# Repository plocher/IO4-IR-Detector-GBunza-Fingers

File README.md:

# IO4-IR-Detector-GBunza-Fingers
## License: CERN Open Hardware Licence v1.2

IR Detector subassemblies made to look like N or HO scale ties.

Works with GBunza\'s MRCS [MRCS-DAPD](/pages/MRCS-DAPD) and SPCoast [IO4-IR-Detector-GBunza](/pages/IO4-IR-Detector-GBunza) passive IR Detectors

  * E1C is the Ambient transistor, labeled T1 on the MRCS schematic.
  * E2C is the between the rails detector transistor.
  * Fab with a BLACK silk screen to help blend in to the trackwork.
  * Cut to length for N scale

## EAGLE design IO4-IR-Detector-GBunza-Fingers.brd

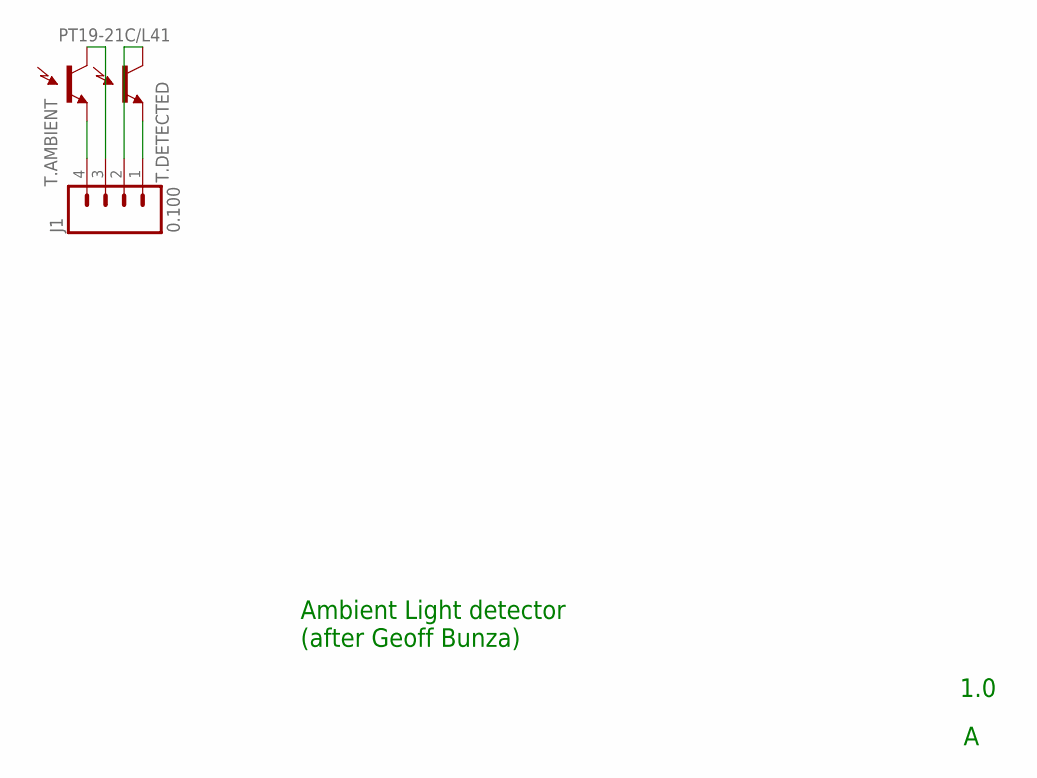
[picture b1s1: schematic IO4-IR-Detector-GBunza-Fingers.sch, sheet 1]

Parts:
J1: 0.100; 1X04_LOCK
T.AMBIENT, T.DETECTED: PT19-21C/L41; ALS-PT19

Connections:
unnamed: J1.4, T.AMBIENT.E (E1)
unnamed: J1.1, T.DETECTED.E (E1)
unnamed: J1.2, T.DETECTED.C (C1)
unnamed: J1.3, T.AMBIENT.C (C1)

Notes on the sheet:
Ambient Light detector (after Geoff Bunza)
1.0

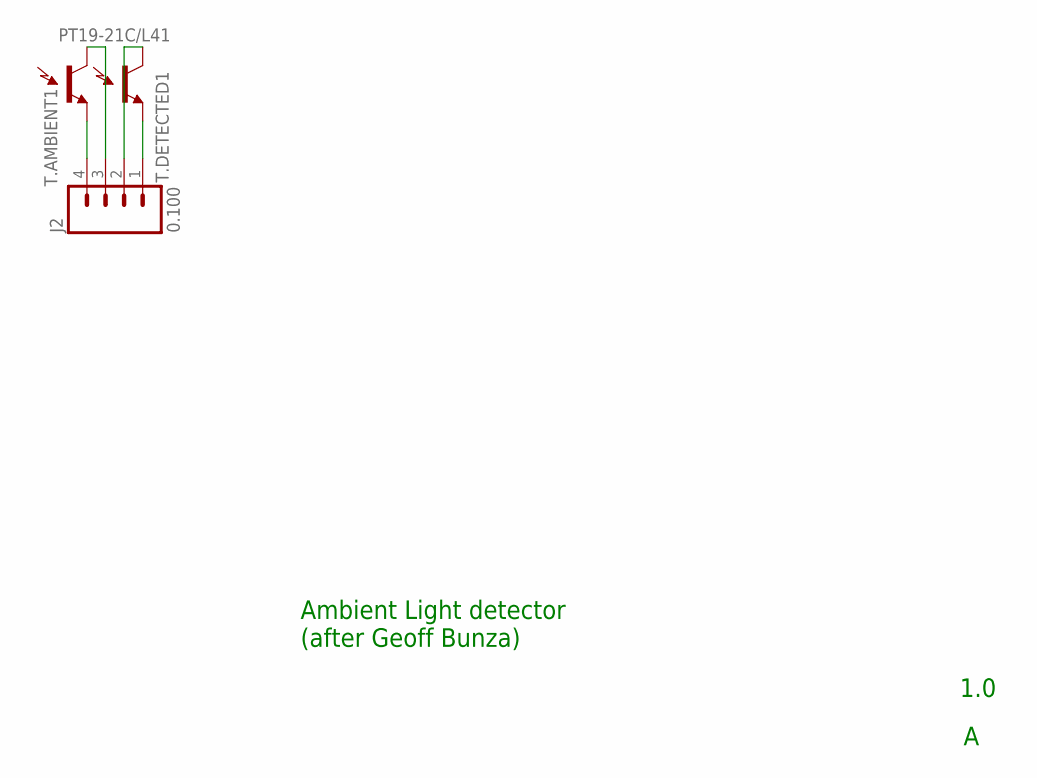
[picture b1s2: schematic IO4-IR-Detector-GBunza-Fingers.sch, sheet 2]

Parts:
J2: 0.100; 1X04_LOCK
T.AMBIENT1, T.DETECTED1: PT19-21C/L41; ALS-PT19

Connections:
unnamed: J2.4, T.AMBIENT1.E (E1)
unnamed: J2.1, T.DETECTED1.E (E1)
unnamed: J2.2, T.DETECTED1.C (C1)
unnamed: J2.3, T.AMBIENT1.C (C1)

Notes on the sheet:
Ambient Light detector (after Geoff Bunza)
1.0

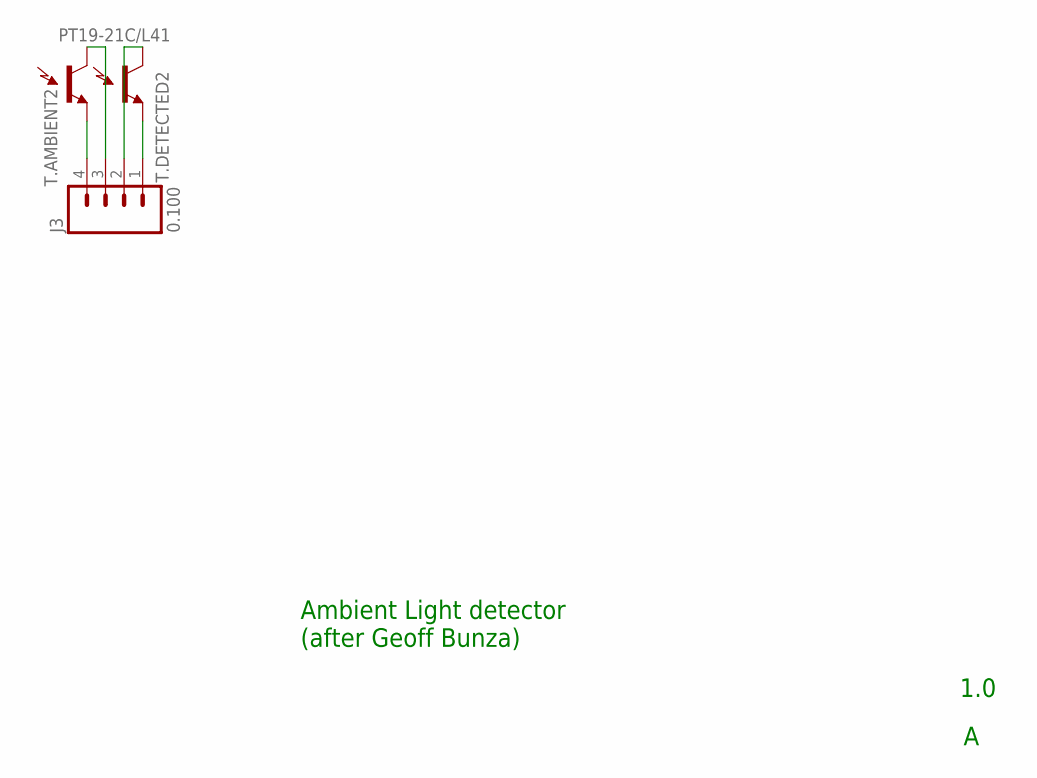
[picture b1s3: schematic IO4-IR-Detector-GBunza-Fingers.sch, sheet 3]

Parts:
J3: 0.100; 1X04_LOCK
T.AMBIENT2, T.DETECTED2: PT19-21C/L41; ALS-PT19

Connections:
unnamed: J3.4, T.AMBIENT2.E (E1)
unnamed: J3.1, T.DETECTED2.E (E1)
unnamed: J3.2, T.DETECTED2.C (C1)
unnamed: J3.3, T.AMBIENT2.C (C1)

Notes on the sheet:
Ambient Light detector (after Geoff Bunza)
1.0

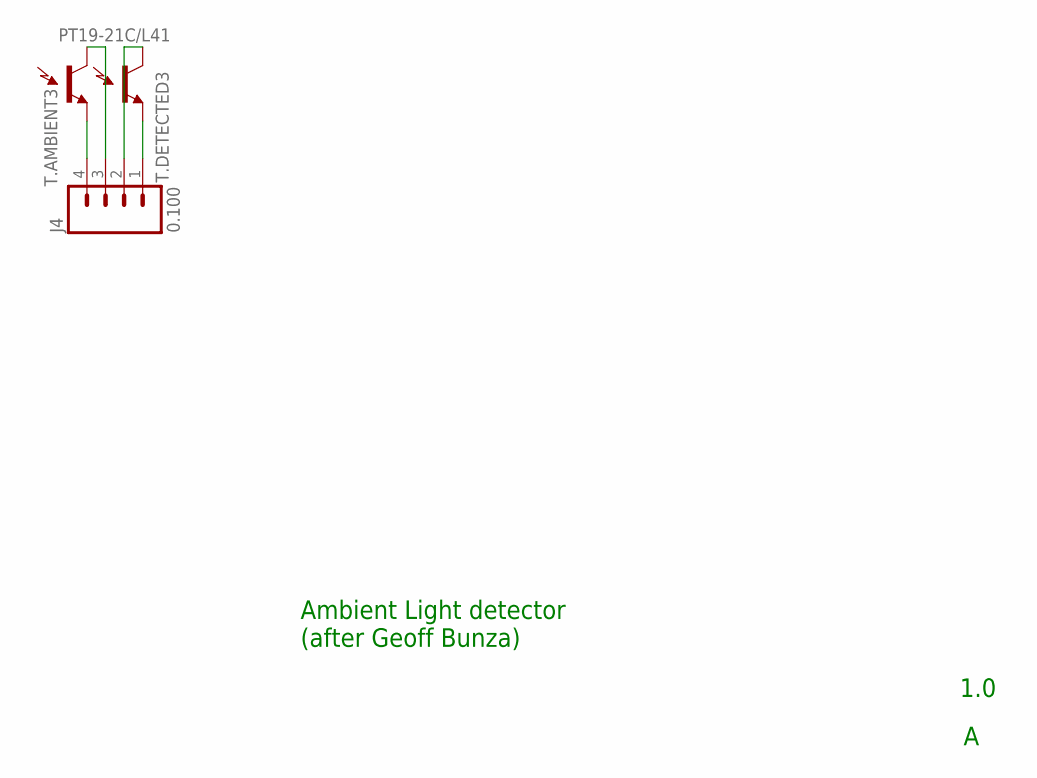
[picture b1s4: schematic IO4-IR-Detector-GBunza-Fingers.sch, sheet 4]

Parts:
J4: 0.100; 1X04_LOCK
T.AMBIENT3, T.DETECTED3: PT19-21C/L41; ALS-PT19

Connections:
unnamed: J4.4, T.AMBIENT3.E (E1)
unnamed: J4.1, T.DETECTED3.E (E1)
unnamed: J4.2, T.DETECTED3.C (C1)
unnamed: J4.3, T.AMBIENT3.C (C1)

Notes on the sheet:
Ambient Light detector (after Geoff Bunza)
1.0

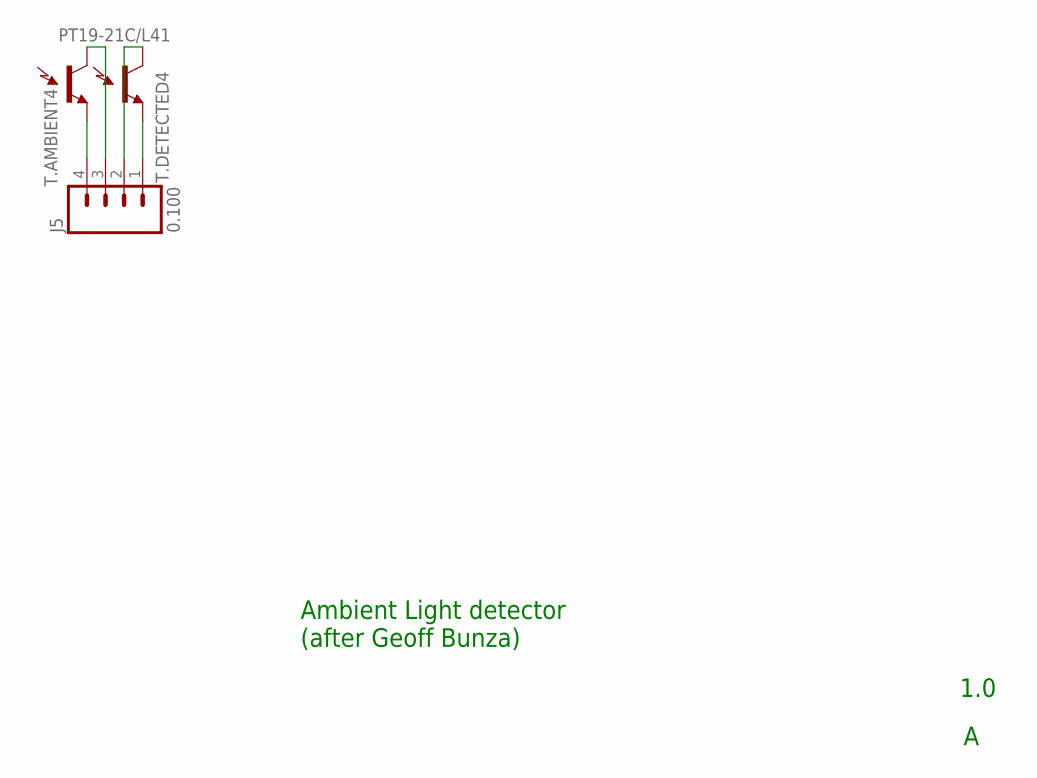
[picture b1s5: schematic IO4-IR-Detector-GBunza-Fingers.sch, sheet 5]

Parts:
J5: 0.100; 1X04_LOCK
T.AMBIENT4, T.DETECTED4: PT19-21C/L41; ALS-PT19

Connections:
unnamed: J5.4, T.AMBIENT4.E (E1)
unnamed: J5.1, T.DETECTED4.E (E1)
unnamed: J5.2, T.DETECTED4.C (C1)
unnamed: J5.3, T.AMBIENT4.C (C1)

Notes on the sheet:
Ambient Light detector (after Geoff Bunza)
1.0

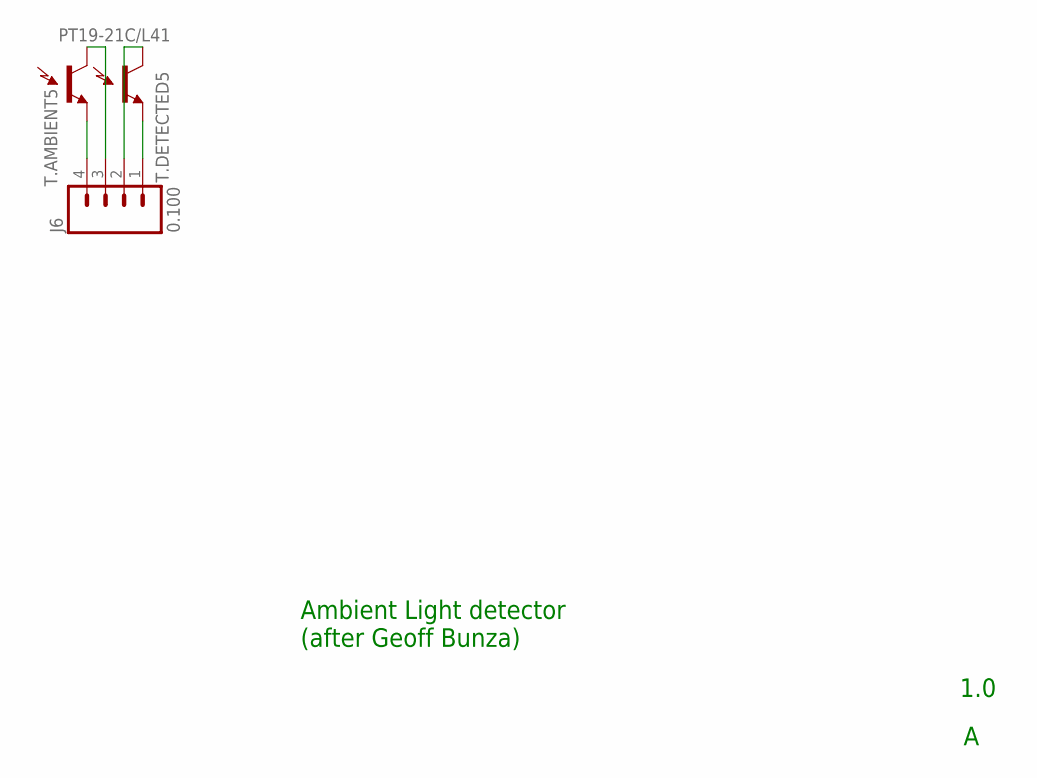
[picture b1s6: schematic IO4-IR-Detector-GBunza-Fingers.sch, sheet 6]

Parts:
J6: 0.100; 1X04_LOCK
T.AMBIENT5, T.DETECTED5: PT19-21C/L41; ALS-PT19

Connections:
unnamed: J6.4, T.AMBIENT5.E (E1)
unnamed: J6.1, T.DETECTED5.E (E1)
unnamed: J6.2, T.DETECTED5.C (C1)
unnamed: J6.3, T.AMBIENT5.C (C1)

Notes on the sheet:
Ambient Light detector (after Geoff Bunza)
1.0

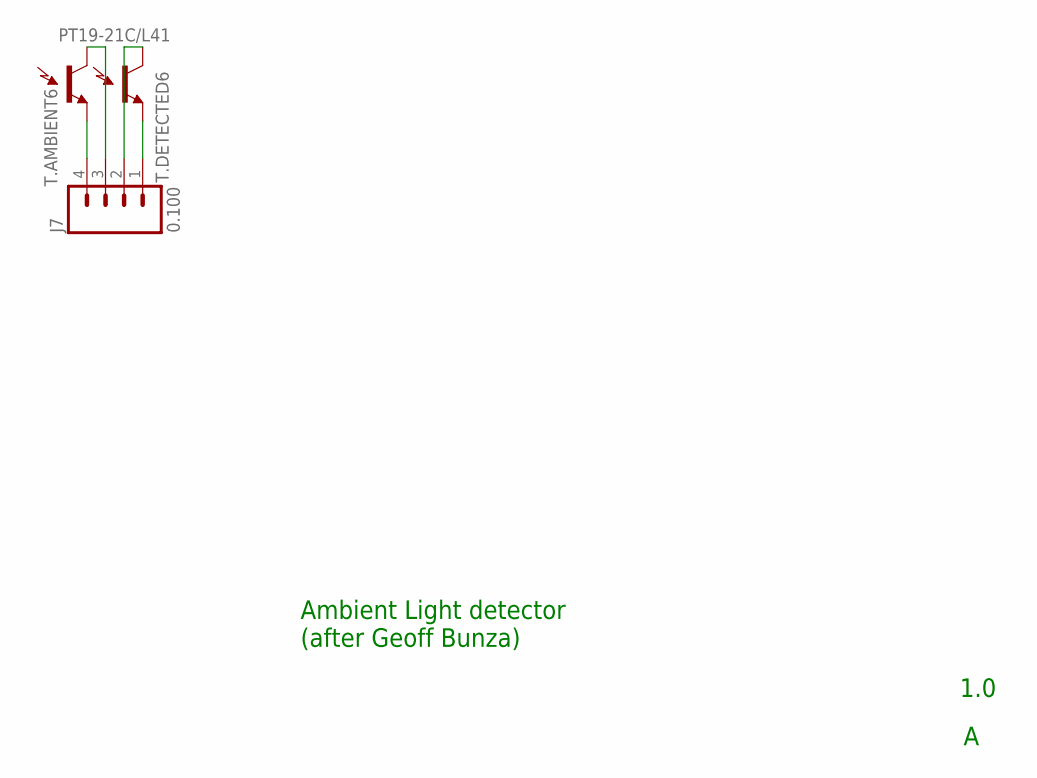
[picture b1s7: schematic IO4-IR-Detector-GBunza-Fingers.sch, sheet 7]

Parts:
J7: 0.100; 1X04_LOCK
T.AMBIENT6, T.DETECTED6: PT19-21C/L41; ALS-PT19

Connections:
unnamed: J7.4, T.AMBIENT6.E (E1)
unnamed: J7.1, T.DETECTED6.E (E1)
unnamed: J7.2, T.DETECTED6.C (C1)
unnamed: J7.3, T.AMBIENT6.C (C1)

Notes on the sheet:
Ambient Light detector (after Geoff Bunza)
1.0

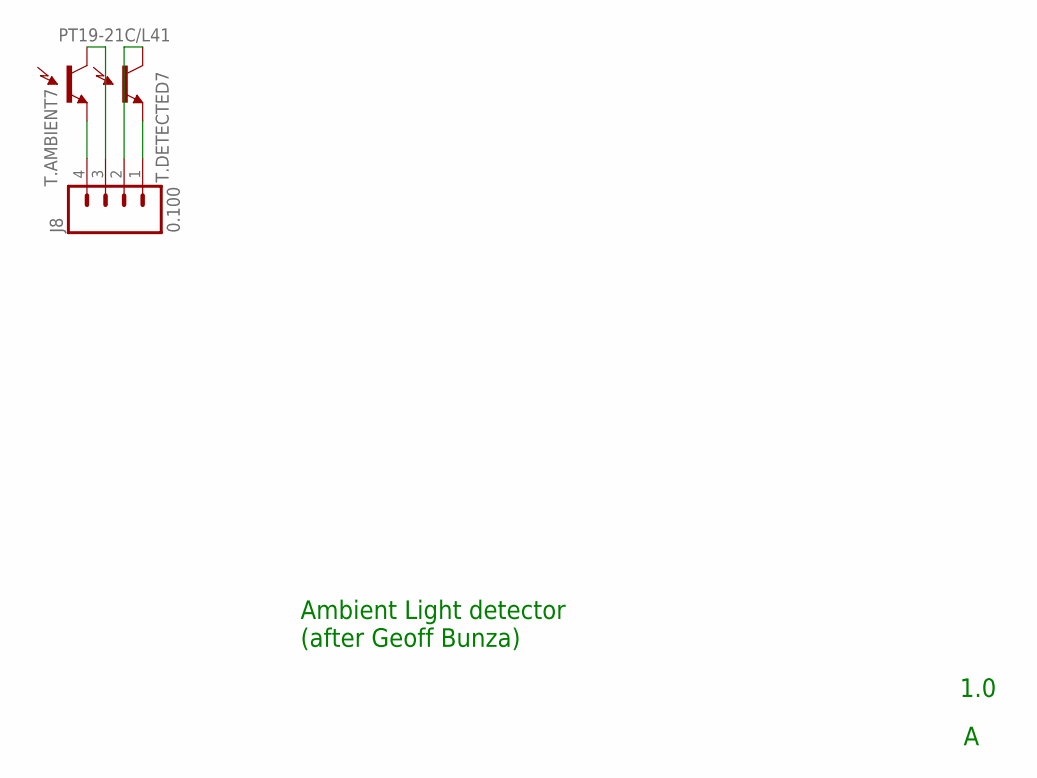
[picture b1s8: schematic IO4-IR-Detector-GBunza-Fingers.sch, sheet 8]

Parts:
J8: 0.100; 1X04_LOCK
T.AMBIENT7, T.DETECTED7: PT19-21C/L41; ALS-PT19

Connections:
unnamed: J8.4, T.AMBIENT7.E (E1)
unnamed: J8.1, T.DETECTED7.E (E1)
unnamed: J8.2, T.DETECTED7.C (C1)
unnamed: J8.3, T.AMBIENT7.C (C1)

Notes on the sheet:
Ambient Light detector (after Geoff Bunza)
1.0

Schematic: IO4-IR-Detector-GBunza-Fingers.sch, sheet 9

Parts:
J9: 0.100; 1X04_LOCK
T.AMBIENT8, T.DETECTED8: PT19-21C/L41; ALS-PT19

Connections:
unnamed: J9.4, T.AMBIENT8.E (E1)
unnamed: J9.1, T.DETECTED8.E (E1)
unnamed: J9.2, T.DETECTED8.C (C1)
unnamed: J9.3, T.AMBIENT8.C (C1)

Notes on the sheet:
Ambient Light detector (after Geoff Bunza)
1.0

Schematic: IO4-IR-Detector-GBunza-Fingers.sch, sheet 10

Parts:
J10: 0.100; 1X04_LOCK
T.AMBIENT9, T.DETECTED9: PT19-21C/L41; ALS-PT19

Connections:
unnamed: J10.4, T.AMBIENT9.E (E1)
unnamed: J10.1, T.DETECTED9.E (E1)
unnamed: J10.2, T.DETECTED9.C (C1)
unnamed: J10.3, T.AMBIENT9.C (C1)

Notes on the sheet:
Ambient Light detector (after Geoff Bunza)
1.0

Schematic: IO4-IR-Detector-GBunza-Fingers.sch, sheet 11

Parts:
J11: 0.100; 1X04_LOCK
T.AMBIENT10, T.DETECTED10: PT19-21C/L41; ALS-PT19

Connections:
unnamed: J11.4, T.AMBIENT10.E (E1)
unnamed: J11.1, T.DETECTED10.E (E1)
unnamed: J11.2, T.DETECTED10.C (C1)
unnamed: J11.3, T.AMBIENT10.C (C1)

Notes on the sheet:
Ambient Light detector (after Geoff Bunza)
1.0

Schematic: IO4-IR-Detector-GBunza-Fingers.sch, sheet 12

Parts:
J12: 0.100; 1X04_LOCK
T.AMBIENT11, T.DETECTED11: PT19-21C/L41; ALS-PT19

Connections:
unnamed: J12.4, T.AMBIENT11.E (E1)
unnamed: J12.1, T.DETECTED11.E (E1)
unnamed: J12.2, T.DETECTED11.C (C1)
unnamed: J12.3, T.AMBIENT11.C (C1)

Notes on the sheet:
Ambient Light detector (after Geoff Bunza)
1.0

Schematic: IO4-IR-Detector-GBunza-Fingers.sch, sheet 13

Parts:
J13: 0.100; 1X04_LOCK
T.AMBIENT12, T.DETECTED12: PT19-21C/L41; ALS-PT19

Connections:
unnamed: J13.4, T.AMBIENT12.E (E1)
unnamed: J13.1, T.DETECTED12.E (E1)
unnamed: J13.2, T.DETECTED12.C (C1)
unnamed: J13.3, T.AMBIENT12.C (C1)

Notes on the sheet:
Ambient Light detector (after Geoff Bunza)
1.0

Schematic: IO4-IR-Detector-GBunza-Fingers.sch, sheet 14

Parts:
J14: 0.100; 1X04_LOCK
T.AMBIENT13, T.DETECTED13: PT19-21C/L41; ALS-PT19

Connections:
unnamed: J14.4, T.AMBIENT13.E (E1)
unnamed: J14.1, T.DETECTED13.E (E1)
unnamed: J14.2, T.DETECTED13.C (C1)
unnamed: J14.3, T.AMBIENT13.C (C1)

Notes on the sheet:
Ambient Light detector (after Geoff Bunza)
1.0

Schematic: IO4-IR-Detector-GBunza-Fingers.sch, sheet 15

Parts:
J15: 0.100; 1X04_LOCK
T.AMBIENT14, T.DETECTED14: PT19-21C/L41; ALS-PT19

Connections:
unnamed: J15.4, T.AMBIENT14.E (E1)
unnamed: J15.1, T.DETECTED14.E (E1)
unnamed: J15.2, T.DETECTED14.C (C1)
unnamed: J15.3, T.AMBIENT14.C (C1)

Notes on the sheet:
Ambient Light detector (after Geoff Bunza)
1.0

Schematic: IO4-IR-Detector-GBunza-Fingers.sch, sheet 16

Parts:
J16: 0.100; 1X04_LOCK
T.AMBIENT15, T.DETECTED15: PT19-21C/L41; ALS-PT19

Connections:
unnamed: J16.4, T.AMBIENT15.E (E1)
unnamed: J16.1, T.DETECTED15.E (E1)
unnamed: J16.2, T.DETECTED15.C (C1)
unnamed: J16.3, T.AMBIENT15.C (C1)

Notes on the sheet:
Ambient Light detector (after Geoff Bunza)
1.0

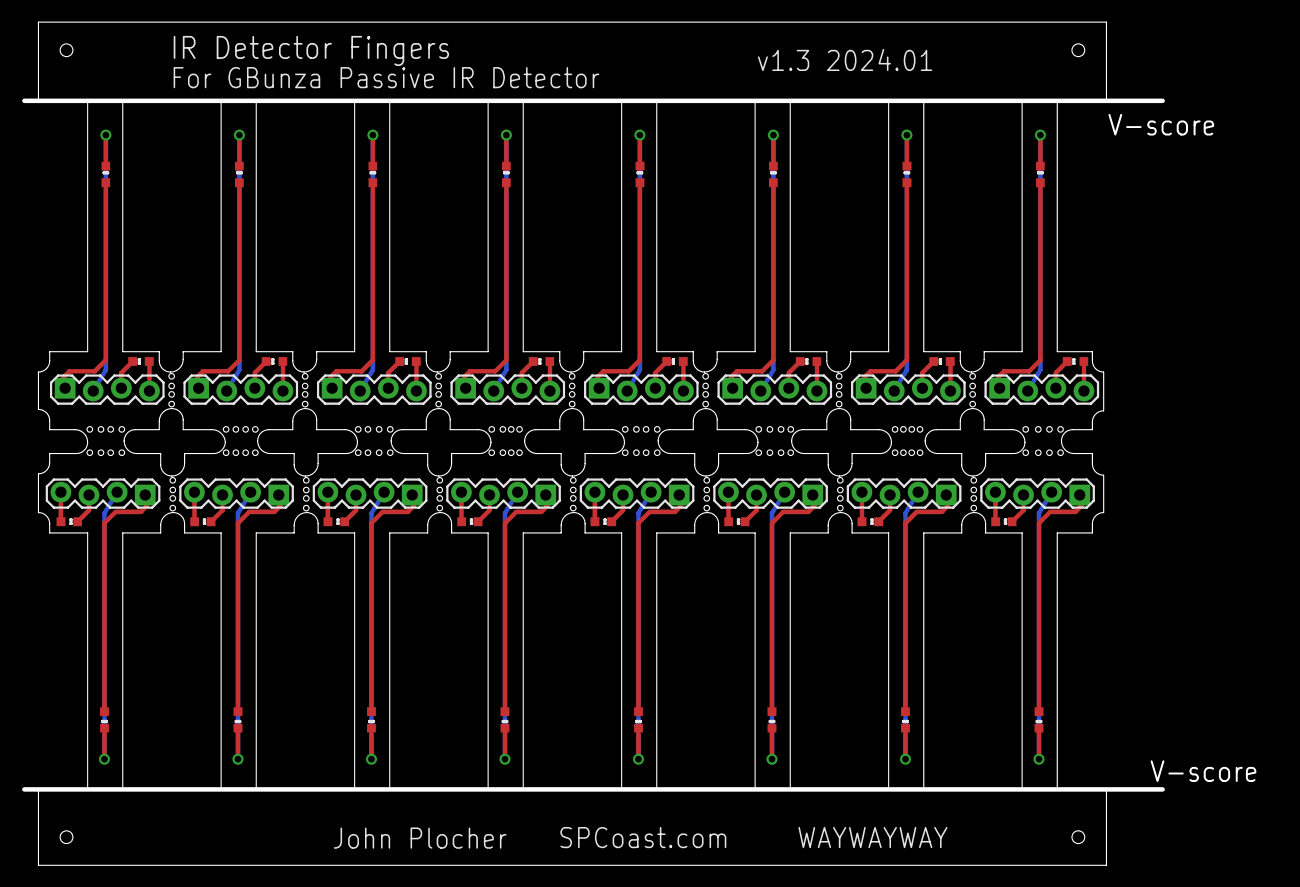
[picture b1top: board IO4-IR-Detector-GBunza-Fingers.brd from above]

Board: 2 copper layers, 102.9 x 76.2 mm, 52 parts (0 on the bottom side), 64 nets.

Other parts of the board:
U$1, U$2, U$3, U$4: MOUNTINGHOLE-TOOL

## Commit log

2019-11-25 1.0-panel
2019-11-25 1.1-panel
2019-12-09 added graphic
2020-05-04 updated tags
2020-10-05 added values for connectors
2022-02-23 replace vscore w/mouse bites, enlarge for fab
2022-02-23 add JLC Fab info
2024-01-14 Version 1.3

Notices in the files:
parts and their libraries:
SparkFun-Sensors: Licensing: Creative Commons ShareAlike 4.0 International - https://creativecommons.org/licenses/by-sa/4.0
